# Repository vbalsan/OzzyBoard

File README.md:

# OzzyBoard
Allwinner V3s prototype SBC

Features : 
- Allwinner V3s SoC 1.2Ghz cortex-A with 64MB ram
- STM32F0, accessible through i2c and UART
- Interface for 0.91" OLED screen
- CH340N for serial through USB
- 40 pin screen interface for Adafruit 7"
- Audio with 3.5mm jack
- 8GB eMMC

Update 15/01/2024
Received the Rev B, changes are in the readme of its folder, main improvements are :
- Ethernet port right side
- Changed power supply of Serial to USB chip for the board own power, no accidental pull down now
- Heartbeat led added
- Added +5V port
- Added buttons
- EEPROM
- More leds...

Update 31/07/2023
- I realized that the LED I added for RX on UART0 is pulling the signal down if no USB with power is connected, resulting in getting stuck in uboot prompt at start, I will desolder it.
- forgot pull-up for I2C, so PMIC was impossible to talk to, fixed with internal pull-up in device tree.
- Tested LCD backlight, it works
- Tested LED on the back side with PWM, works fine too, I may use that with a kernel module to signal statuses. (uploaded a pic for it)
- Need to try transfering Uboot and Linux on eMMC

Update 05/05/2023
- Ethernet port LNK led is not working, mixed up connections, the eth connector has pin 9 as anode and 10 cathode, but on Kicad this was inverted.
- Board booting fine with kernel 6.1
- Made a custom device tree but with sunxi dtsi
- eMMC can be partitioned and formatted, perf test show +/- 40MB/s write or read
- Ethernet works, need to configure /etc/network/interfaces and add it to rootfs overlay though

Update 23/04/2023 :
- Ethernet port is inverted... 3D model on kicad was not accurate, lesson learned. Will replace with vertical models
- Green external led for LNK is too bright, Vf is equal to 2.7V for a forward current of 1mA and not typical 3V, so current in the end is more like 2mA
- Didn't test screen, need to update BSP with new device tree
- Power consumption is around 80mA, not bad

Board received : 

Board with vital LEDs :

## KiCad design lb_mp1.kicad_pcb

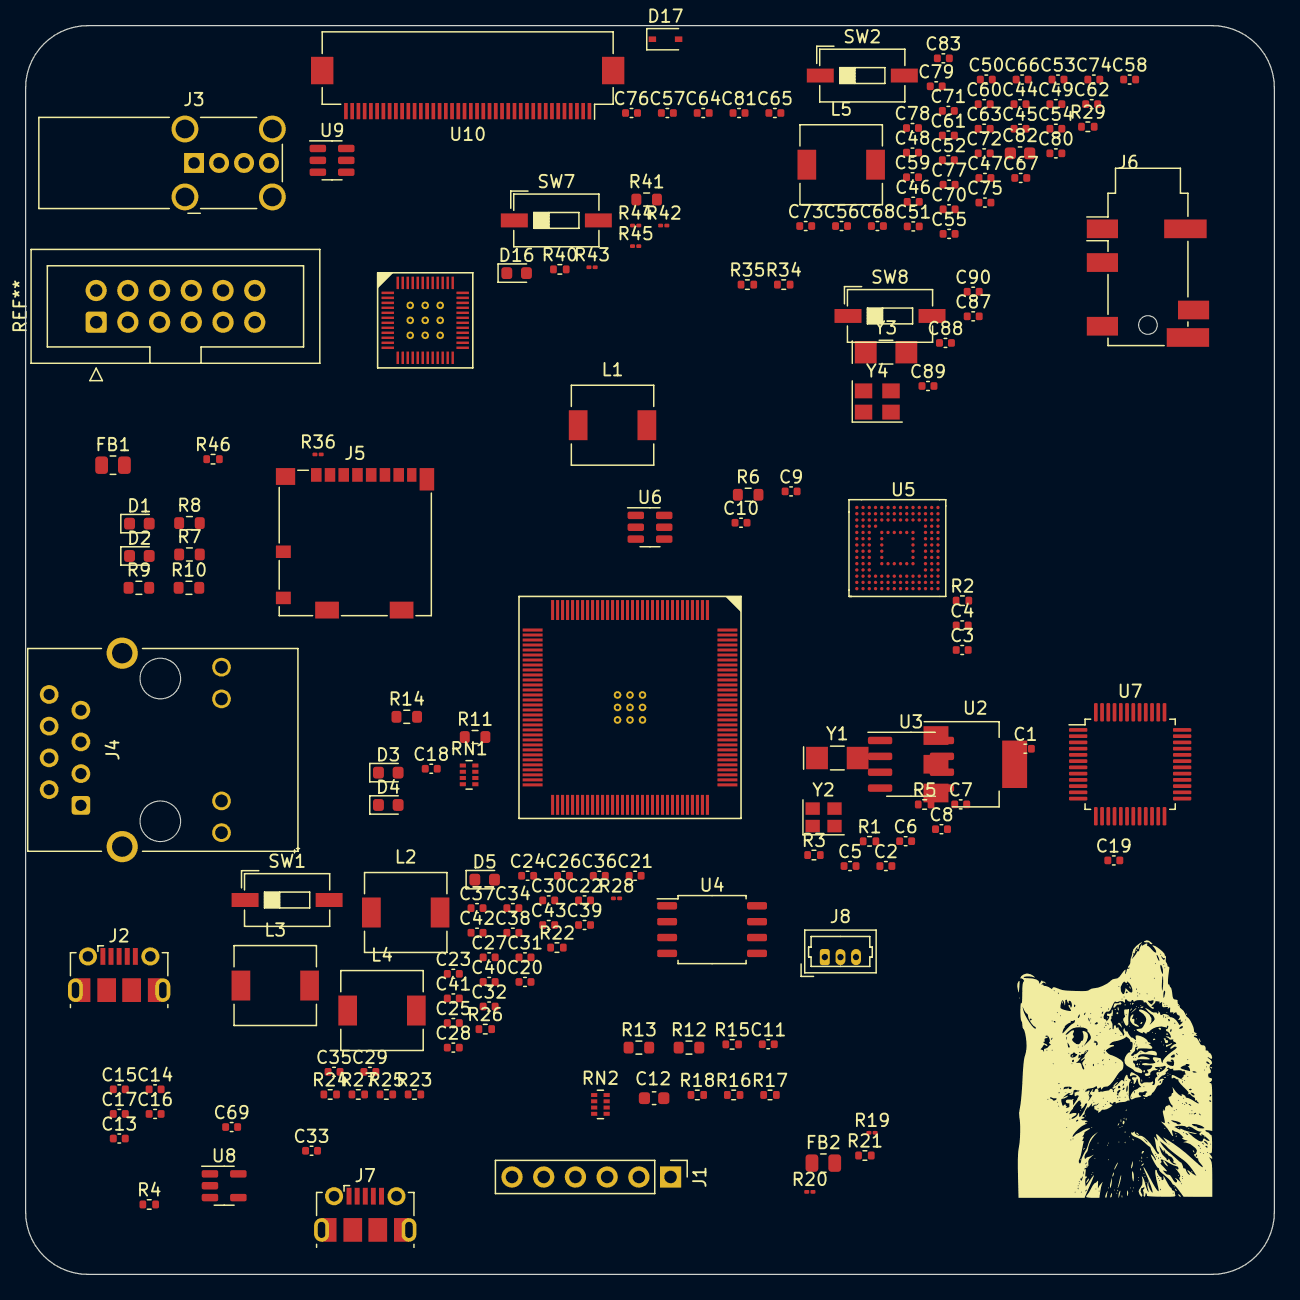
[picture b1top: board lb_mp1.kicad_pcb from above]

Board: 2 copper layers, 100.0 x 100.0 mm, 169 parts (0 on the bottom side), 124 nets, no tracks yet.

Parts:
C1, C5, C6, C9, C10, C22, C27, C29, C31, C32, C34, C35, C36, C37, C38, C41, C42, C43, C44, C46, C47, C48, C49, C50, C51, C53, C55: 100n; C_0402_1005Metric
C2, C14, C15: 0.1uF; C_0402_1005Metric
C3, C4, C7, C8, C89, C90: 18pf; C_0402_1005Metric
C11, C18, C19, C21, C40, C45, C67: 10u; C_0402_1005Metric
C12: 100n; C_0603_1608Metric
C13: C; C_0402_1005Metric
C16, C17: 3.3uF; C_0402_1005Metric
C20, C23, C24, C25, C26, C28, C30, C39: 1u; C_0402_1005Metric
C33: 10n; C_0402_1005Metric
C52, C56, C61, C63, C65, C66, C74, C75, C76, C79, C81: 10uF; C_0402_1005Metric
C54, C58, C59, C60, C80: 4.7uF; C_0402_1005Metric
C57, C68, C72, C78: 1uF; C_0402_1005Metric
C62, C64: 1nF; C_0402_1005Metric
C69: 100uF; C_0402_1005Metric
C70: 4.7u; C_0402_1005Metric
C71, C77: 100pF; C_0402_1005Metric
C73, C83: 0.22uF; C_0402_1005Metric
C82: 10uF; C_0603_1608Metric
C87, C88: 12pf; C_0402_1005Metric
D1, D2, D3, D4, D5, D16: LED; LED_0603_1608Metric
D17: 1N5819WS; D_SOD-323
FB1, FB2: FerriteBead; R_0805_2012Metric
J1: UART_Header; PinHeader_1x06_P2.54mm_Vertical
J2: SERIAL; USB_Micro-B_Molex-105017-0001
J3: USB_HOST; USB_A_Wuerth_614004134726_Horizontal
J4: RJ45_LED_Shielded; RJ45_Hanrun_HR911105A
J5: Micro_SD_Card; microSD_HC_Molex_104031-0811
J6: AudioJack4_SwitchTR1; Jack_3.5mm_PJ31060-I_Horizontal
J7: USB_POWER; USB_Micro-B_Molex-105017-0001
J8: Bat; Molex_PicoBlade_53047-0310_1x03_P1.25mm_Vertical
L1: 10uH; L_6.3x6.3_H3
L2, L3, L4, L5: 4.7uH 1.1A 0.1R; L_6.3x6.3_H3
R1, R26, R40: 0R; R_0402_1005Metric
R2, R27: 22R; R_0402_1005Metric
R3, R21, R29: 47k; R_0402_1005Metric
R4: 0.5; R_0402_1005Metric
R5: 10M; R_0402_1005Metric
R6: 6k; R_0603_1608Metric
R7, R8, R9, R10: 49.9; R_0603_1608Metric
R11: 1K; R_0603_1608Metric
R12, R13, R14: 1k; R_0603_1608Metric
R15, R16, R17, R18, R23, R46: 10k; R_0402_1005Metric
R19, R20: 470; R_01005_0402Metric
R22, R24, R25, R34, R35: 33R; R_0402_1005Metric
R28, R45: 10k; R_01005_0402Metric
R36, R42: 1k; R_01005_0402Metric
R41: 0.03R; R_0603_1608Metric
R43: 200k 1%; R_01005_0402Metric
R44: 47k; R_01005_0402Metric
RN1, RN2: 10k; R_Array_Concave_4x0402
SW1, SW2, SW7, SW8: SW_SPDT; SW_DIP_SPSTx01_Slide_6.7x4.1mm_W6.73mm_P2.54mm_LowProfile_J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
U1: V3S-split; V3s-ELQFP-128
U2: AMS1117-3.3; SOT-223-3_TabPin2
U3: CH340N; SOIC-8_3.9x4.9mm_P1.27mm
U4: W25Q128JVS; SOIC-8_5.23x5.23mm_P1.27mm
U5: FEMDRM008G-58A39_NO_NC; EMMC_JLCP
U6: SRV05-4; SOT-23-6
U7: STM32F030C8Tx; LQFP-48_7x7mm_P0.5mm
U8: SY8088AAC; SOT-23-5
U9: SY7200AABC; SOT-23-6
U10: FPC_40; Hirose_FH12-40S-0.5SH_1x40-1MP_P0.50mm_Horizontal
U11: AXP209; AXP209-QFN48
Y1, Y3: 32.768khz; Crystal_SMD_MicroCrystal_CC7V-T1A-2Pin_3.2x1.5mm_HandSolder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
Y2: 24MHz; Crystal_SMD_2520-4Pin_2.5x2.0mm
Y4: 16MHz; Crystal_SMD_3225-4Pin_3.2x2.5mm

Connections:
+1V2: C11.1, C18.1, C20.1, C23.1, C24.1, C29.1, C30.1, C36.1, C37.1, C41.1, C42.1, C46.1, C47.1, C61.1, C62.1, L3.1, U1.19 (VDD-SYS3), U1.20 (VDD-CPU3), U1.21 (VDD-CPU2), U1.25 (VDD-CPU1), U1.26 (VDD-CPU0), U1.38 (VDD-CPU4), U1.47 (VDD-CPU5), U1.51 (VDD-CPU6), U1.56 (VDD-CPU7), U1.58 (VDD-SYS4), U1.64 (VDD-SYS5), U1.80 (VDD-SYS0), U1.88 (EPHY-VDD), U1.108 (VDD-SYS1), U1.126 (VDD-SYS2), U11.10 (DCDC2)
+1V8: C21.1, C26.1, C32.1, C39.1, C43.1, C50.1, C53.1, C55.1, C56.1, L2.2, U1.59 (VCC-DRAM8), U1.60 (VCC-DRAM9), U1.61 (VCC-DRAM10), U1.62 (VCC-DRAM11), U1.65 (VCC-DRAM0), U1.66 (VCC-DRAM1), U1.67 (VCC-DRAM2), U1.68 (VCC-DRAM3), U1.69 (VCC-DRAM4), U1.70 (VCC-DRAM5), U1.72 (VCC-DRAM6), U1.79 (VCC-DRAM7)
+3.3V: C5.1, C12.1, C14.1, C15.1, C16.1, C17.1, C19.1, C22.1, C25.1, C27.1, C28.1, C31.1, C38.1, C44.1, C63.1, C64.1, C65.1, C66.1, FB2.2, J5.4 (VDD), L1.1, L4.1, R15.1, R16.1, R17.1, R18.1, R19.1, R20.1, R23.1, R46.1, RN1.1 (common), RN2.1 (common), SW8.1 (A), U1.12 (VCC-PE0), U1.29 (VCC-PE1), U1.50 (VCC-IO3), U1.57 (VCC-IO2), U1.85 (VCC-MCSI), U1.93 (EPHY-VCC), U1.104 (VCC-IO0), U1.127 (VCC-IO1), U4.8 (VCC), U5.C6 (VCCQ), U5.E6 (VCC), U5.F5 (VCC), U5.J10 (VCC), U5.K9 (VCC), U5.M4 (VCCQ), U5.N4 (VCCQ), U5.P3 (VCCQ), U5.P5 (VCCQ), U7.1 (VDD), U7.24 (VDD), U7.48 (VDD), U10.4 (VDD), U11.13 (LDO24IN), U11.17 (DCDC3), U11.40 (LDO3IN)
+3V0: C35.1, C40.1, C48.1, C58.2, U1.76 (VCC-PLL), U1.115 (AVCC), U11.12 (LDO2)
+BATT: C78.1, C81.1, J8.1, R41.2, U11.38 (BAT@1), U11.39 (BAT@2), U11.42 (BATSENSE)
+VDC: C33.1, C45.1, C49.1, C67.2, J7.1 (VBUS), U11.32 (ACIN@1), U11.33 (ACIN@2)
GND: C1.2, C2.2, C3.2, C4.2, C5.2, C7.2, C8.2, C9.2, C10.2, C11.2, C12.2, C13.2, C14.2, C15.2, C16.2, C17.2, C18.2, C19.2, C20.2, C21.2, C22.2, C23.2, C24.2, C25.2, C26.2, C27.2, C28.2, C29.2, C30.2, C31.2, C32.2, C33.2, C34.2, C35.2, C36.2, C37.2, C38.2, C39.2, C40.2, C41.2, C42.2, C43.2, C44.2, C45.2, C46.2, C47.2, C48.2, C49.2, C51.2, C52.2, C54.1, C55.2, C56.2, C57.1, C58.1, C59.1, C60.2, C61.2, C62.2, C63.2, C64.2, C65.2, C66.2, C67.1, C68.1, C69.1, C70.1, C71.1, C72.2, C73.2, C74.2, C75.2, C76.2, C77.1, C79.2, C80.2, C81.2, C82.2, C83.2, C87.2, C88.2, C89.2, C90.2, D1.1 (K), D2.1 (K), J1.1, J2.5 (GND), J2.6 (Shield), J3.4 (GND), J3.5 (Shield), J4.8, J4.9, J4.11, J4.SH, J5.6 (VSS), J5.9 (SHIELD), J7.5 (GND), J7.6 (Shield), J8.2, R2.1, R3.2, R6.2, R21.2, R27.1, R29.2, R36.1, R43.1, SW1.2 (B), SW2.2 (B), SW7.2 (B), U1.116 (AGND), U1.GND$1 (EGND), U1.GND$2 (EGND), U1.GND$3 (EGND), U1.GND$4 (EGND), U1.GND$5 (EGND), U1.GND$6 (EGND), U1.GND$7 (EGND), U1.GND$8 (EGND), U1.GND$9 (EGND), U2.1 (GND), U3.3 (GND), U4.4 (GND), U5.A6 (VSS), U5.C4 (VSSQ), U5.E7 (VSS), U5.G5 (VSS), U5.H10 (VSS), U5.J5 (VSS), U5.K8 (VSS), U5.N2 (VSSQ), U5.N5 (VSSQ), U5.P4 (VSSQ), U5.P6 (VSSQ), U6.2 (VN), U7.8 (VSSA), U7.23 (VSS), U7.47 (VSS), U8.2 (GND), U9.2 (GND), U10.3 (GND), U10.5 (R0), U10.6 (R1), U10.13 (G0), U10.14 (G1), U10.21 (B0), U10.22 (B1), U10.29 (GND), U10.36 (GND), U11.6 (N_VBUSEN), U11.9 (PGND2), U11.16 (PGND3), U11.22 (AGND), U11.37 (TS), U11.46 (PGND1), U11.GND$1 (EP), U11.GND$2 (EP), U11.GND$3 (EP), U11.GND$4 (EP), U11.GND$5 (EP), U11.GND$6 (EP), U11.GND$7 (EP), U11.GND$8 (EP), U11.GND$9 (EP), Y2.2, Y2.4, Y4.2, Y4.4
LNK_LED: R12.2, R14.2, U1.77 (EPHY-LINK-LED)
NMI: U1.39 (PB0/UART2_TX/PB_EINT0), U11.48 (IRQ/WAKEUP)
N_Oe: C71.2, R36.2, U11.4 (N_OE)
unnamed: C1.1, R2.2, U2.2 (VO), U3.8 (V3)
unnamed: C2.1, FB1.2, U2.3 (VI), U3.5 (VCC)
unnamed: C3.1, R5.1, U1.96 (X32KIN), Y1.2
unnamed: C4.1, R5.2, U1.95 (X32KOUT), Y1.1
unnamed: C6.1, R27.2
unnamed: C6.2, J6.R2, R26.1, U1.124 (HPCOMFB)
unnamed: C7.1, U1.75 (X24MIN), Y2.1
unnamed: C8.1, U1.74 (X24MOUT), Y2.3
unnamed: C9.1, J4.5, R9.2, R10.2
unnamed: C10.1, J4.4, L1.2, R7.1, R8.1
unnamed: C13.1, U5.C2 (VDDI)
unnamed: C50.2, C51.1, U1.63 (SVREF1), U1.71 (SVREF0)
unnamed: C53.2, U8.5 (FB)
unnamed: C54.2, U1.97 (RTC-VIO)
unnamed: C59.2, U11.41 (LDO3)
unnamed: C60.1, U11.11 (LDO4)
unnamed: C68.2, U11.24 (VREF)
unnamed: C69.2, U11.30 (BACKUP)
unnamed: C70.2, U11.19 (GPIO0)
unnamed: C72.1, U11.26 (VINT), U11.27 (LDO1SET)
unnamed: C78.2, C79.1, L5.2, R41.1, U11.43 (CHSENSE)
unnamed: C80.1, R40.2, U11.31 (VBUS)
unnamed: D17.1 (K), U9.5 (OVR), U10.2 (LEDA)
unnamed: C88.1, Y4.3
unnamed: D1.2 (A), R13.1
unnamed: D2.2 (A), R14.1
unnamed: D4.1 (K), J1.4, U1.49 (PB9/TWI1_SDA/UART0_RX/PB_EINT9), U3.6 (TXD)
unnamed: D4.2 (A), R19.2
unnamed: D5.1 (K), J1.5, U1.48 (PB8/TWI1_SCK/UART0_TX/PB_EINT8), U3.7 (RXD)
unnamed: D5.2 (A), R20.2, R28.2
unnamed: J5.5 (CLK), R22.1
unnamed: J5.1 (DAT2), R23.2, R34.1, U1.101 (PF5/SDC0_D2/JTAG_CK1)
unnamed: J5.2 (DAT3/CD), R35.1, RN1.2 (R1), U1.102 (PF4/SDC0_D3/UART0_RX)
unnamed: J5.3 (CMD), RN1.3 (R2), U1.103 (PF3/SDC0_CMD/JTAG_DO1)
unnamed: J5.7 (DAT0), RN1.4 (R3), U1.106 (PF1/SDC0_D0/JTAG_DI1)
unnamed: J5.8 (DAT1), R15.2, RN1.5 (R4), U1.107 (PF0/SDC0_D1/JTAG_MS1)
unnamed: J6.T, R25.1
unnamed: J6.R1, R24.1
unnamed: D16.1 (K), U11.36 (CHGLED)
unnamed: D16.2 (A), R45.2
unnamed: D17.2 (A), U9.1 (LX)
unnamed: FB1.1, J2.1 (VBUS)
unnamed: FB2.1, U7.9 (VDDA)
unnamed: J2.2 (D-), U3.2 (UD-)
unnamed: J2.3 (D+), U3.1 (UD+)
unnamed: J2.4 (ID), R21.1
unnamed: J3.2 (D-), U1.110 (USB-DM), U6.3 (IO2)
unnamed: J3.3 (D+), U1.111 (USB-DP), U6.1 (IO1)
unnamed: J4.1, R7.2, U1.92 (EPHY-TXP)
unnamed: J4.2, R8.2, U1.91 (EPHY-TXN)
unnamed: J4.3, R9.1, U1.90 (EPHY-RXP)
unnamed: J4.6, R10.1, U1.89 (EPHY-RXN)
unnamed: J4.10, R12.1
unnamed: J4.12, R11.1
unnamed: J7.4 (ID), R29.1
unnamed: L2.1, U8.3 (LX)
unnamed: L3.2, U11.8 (LX2)
unnamed: L4.2, U11.15 (LX3)
unnamed: L5.1, U11.45 (LX1)
unnamed: R6.1, U1.94 (EPHY-RTX)
unnamed: R16.2, U1.54 (PC2/SDC2_RST/SPI_CS), U4.1 (~CS)
unnamed: R17.2, U1.4 (PG1/SDC1_CMD/PG_EINT1), U5.M5 (CMD)
unnamed: R18.2, U5.K5 (RSTN)
unnamed: R22.2, U1.105 (PF2/SDC0_CLK/UART0_TX)
unnamed: R24.2, U1.121 (HPOUTL)
unnamed: R25.2, U1.120 (HPOUTR)
unnamed: R26.2, U1.125 (HPCOM)
unnamed: R35.2, U1.73 (SZQ)
unnamed: U9.3 (FB), U10.1 (LEDK)
unnamed: R43.2, U11.23 (BIAS)
unnamed: RN2.2 (R1), U1.3 (PG2/SDC1_D0/PG_EINT2), U5.A3 (DAT0)
unnamed: RN2.3 (R2), U1.2 (PG3/SDC1_D1/PG_EINT3), U5.A4 (DAT1)
unnamed: RN2.4 (R3), U1.1 (PG4/SDC1_D2/PG_EINT4), U5.A5 (DAT2)
unnamed: RN2.5 (R4), U1.128 (PG5/SDC1_D3/PG_EINT5), U5.B2 (DAT3)
unnamed: U1.5 (PG0/SDC1_CLK/PG_EINT0), U5.M6 (CLK)
unnamed: U1.6 (PE24/LCD_D23), U10.12 (R7)
unnamed: U1.7 (PE23/LCD_D22), U10.11 (R6)
unnamed: U1.11 (PE19/CSI_D15/LCD_D21), U10.10 (R5)
unnamed: U1.13 (PE18/CSI_D14/LCD_D20), U10.9 (R4)
unnamed: U1.14 (PE17/CSI_D13/LCD_D19), U10.8 (R3)
unnamed: U1.15 (PE16/CSI_D12/LCD_D18), U10.7 (R2)
unnamed: U1.16 (PE15/CSI_D11/LCD_D15), U10.20 (G7)
unnamed: U1.17 (PE14/CSI_D10/LCD_D14), U10.19 (G6)
unnamed: U1.18 (PE13/CSI_D9/LCD_D13), U10.18 (G5)
unnamed: U1.22 (PE12/CSI_D8/LCD_D12), U10.17 (G4)
unnamed: U1.23 (PE11/CSI_D7/LCD_D11), U10.16 (G3)
unnamed: U1.24 (PE10/CSI_D6/LCD_D10), U10.15 (G2)
unnamed: U1.27 (PE9/CSI_D5/LCD_D7), U10.28 (B7)
unnamed: U1.28 (PE8/CSI_D4/LCD_D6), U10.27 (B6)
unnamed: U1.30 (PE7/CSI_D3/LCD_D5), U10.26 (B5)
unnamed: U1.31 (PE6/CSI_D2/LCD_D4), U10.25 (B4)
unnamed: U1.32 (PE5/CSI_D1/LCD_D3), U10.24 (B3)
unnamed: U1.33 (PE4/CSI_D0/LCD_D2), U10.23 (B2)
unnamed: U1.34 (PE3/CSI_VSYNC/LCD_VSYNC), U10.33 (VSYNC)
unnamed: U1.35 (PE2/CSI_HSYNC/LCD_HSYNC), U10.32 (HSYNC)
unnamed: U1.36 (PE1/CSI_MCLK/LCD_DE), U10.34 (DEN)
unnamed: U1.37 (PE0/CSI_PCLK-/LCD_CLK), U10.30 (DCLK)
unnamed: U1.52 (PC0/SDC2_CLK/SPI_MISO), U4.2 (DO(IO1))
unnamed: U1.53 (PC1/SDC2_CMD/SPI_CLK), U4.6 (CLK)
unnamed: U1.55 (PC3/SDC2_D0/SPI_MOSI), U4.5 (DI(IO0))
unnamed: R46.2, U4.3 (IO2), U4.7 (IO3)
OSC32_IN: C89.1, U7.3 (PC14), Y3.2
OSC32_OUT: C90.1, U7.4 (PC15), Y3.1
OSC_IN: C87.1, U7.5 (PF0), Y4.1
PWM0: U1.43 (PB4/PWM0/PB_EINT4), U9.4 (EN/PWM)
Pwron: C77.2, R42.2, U11.47 (PWRON)
SPD__LED: R11.2, R13.2, U1.78 (EPHY-SPD-LED)
USART1_RX: U1.9 (PE21/CSI_SCK/TWI1_SCK/UART1_TX), U7.13 (PA3)
USART1_TX: U1.8 (PE22/CSI_SDA/TWI1_SDA/UART1_RX), U7.12 (PA2)
VCC: C52.1, C73.1, C74.1, C75.1, C76.1, C82.1, C83.1, J3.1 (VBUS), R28.1, R40.1, R45.1, U6.5 (VP), U8.4 (VIN), U9.6 (VDD), U11.7 (VIN2), U11.14 (VIN3), U11.21 (APS), U11.29 (DC3SET), U11.34 (IPSOUT@1), U11.35 (IPSOUT@2), U11.44 (VIN1)
VDD: C34.1, C57.2, R44.2, U1.98 (VCC-RTC), U11.28 (LDO1)
reset: R44.1, U1.99 (RESET), U11.25 (PWROK)
scl: U1.45 (PB6/TWI0_SCK/PB_EINT6), U11.2 (SCK)
sda: U1.46 (PB7/TWI0_SDA/PB_EINT7), U11.1 (SDA)

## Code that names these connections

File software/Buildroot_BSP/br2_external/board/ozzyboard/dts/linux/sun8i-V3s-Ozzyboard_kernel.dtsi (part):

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
			/omit-if-no-ref/
			csi1_8bit_pins: csi1-8bit-pins {
				pins = "PE0", "PE2", "PE3", "PE8", "PE9",
				       "PE10", "PE11", "PE12", "PE13", "PE14",
				       "PE15";
				function = "csi";
			};

			/omit-if-no-ref/
			csi1_mclk_pin: csi1-mclk-pin {
				pins = "PE1";
				function = "csi";
			};
			*/
			rgb_pins: rgb_pins {
				pins = "PE0", "PE1", "PE2", "PE3", "PE4", "PE5",
				       "PE6", "PE7", "PE8", "PE9", "PE10", "PE11",
				       "PE12", "PE13", "PE14", "PE15", "PE16", "PE17",
				       "PE18", "PE19", "PE23", "PE24";
				function = "lcd";
			};

			i2c0_pins: i2c0-pins {
				pins = "PB6", "PB7";
				function = "i2c0";
				bias-pull-up;	    /*necessary since I forgot the pull-up*/
			};

			/*no-ref*/			
			i2c1_pb_pins: i2c1-pb-pins {
				pins = "PB8", "PB9";
				function = "i2c1";
			};
			
			i2c1_pe_pins: i2c1-pe-pins {
				pins = "PE21", "PE22";
				function = "i2c1";
			};
			
			
			pwm0_pins: pwm0 {
				pins = "PB4";
				function = "pwm0";
			};
				
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			};

			uart0_pb_pins: uart0-pb-pins {
				pins = "PB8", "PB9";
				function = "uart0";
				bias-pull-up;
			};

			/* used for NMI*/			
			uart2_pins: uart2-pins {
				pins = "PB0", "PB1";
				function = "uart2";
			};
			

			mmc0_pins: mmc0-pins {
				pins = "PF0", "PF1", "PF2", "PF3",
				       "PF4", "PF5";
				function = "mmc0";
				drive-strength = <30>;
				bias-pull-up;
			};

			mmc1_pins: mmc1-pins {
				pins = "PG0", "PG1", "PG2", "PG3",
				       "PG4", "PG5";
				function = "mmc1";
				drive-strength = <30>;
				bias-pull-up;
			};

			spi0_pins: spi0-pins {
				pins = "PC0", "PC1", "PC2", "PC3";
				function = "spi0";
			};
		};
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
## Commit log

2023-03-07 cleaning and naming
2023-03-07 removed old schematics
2023-03-25 PCB done
2023-03-25 added data, picture and BOM
2023-07-22 update schematic pdf
2023-07-31 Adding BSP environment
    Added BSP generation with buildroot and BR2_EXTERNAL
    Device tree modified for LCD and AXP209
    Added Pull-up to I2C
    Added default ETH config
2023-07-31 added buildroot as submodule
2023-08-01 scripts and clean-up
2023-08-01 typo
2023-10-19 kernel 5.3, added packages and LCD drivers
2023-10-21 Added support for SPI, flashrom utility, and tweak to boot from SPI NOR
2023-10-28 added LCD keys, not functionnal
2024-01-05 Change in folder structure and RevB added
    Changes include :
    - Changed the Ethernet port orientation
    - Changed power supply of Serial to USB chip for the board own power, no accidental pull down now.
    - USB ports are more on board.
    - Activity led added with PF6
    - Battery pins are JST compatible
2024-01-05 added all files for RevB
2024-01-18 Removed gerber files, reajusted paths for files, added photo and PDF
